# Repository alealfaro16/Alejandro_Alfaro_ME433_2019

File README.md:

# Alejandro_Alfaro_ME433_2019
Mechatronics 433 projects and Hwks

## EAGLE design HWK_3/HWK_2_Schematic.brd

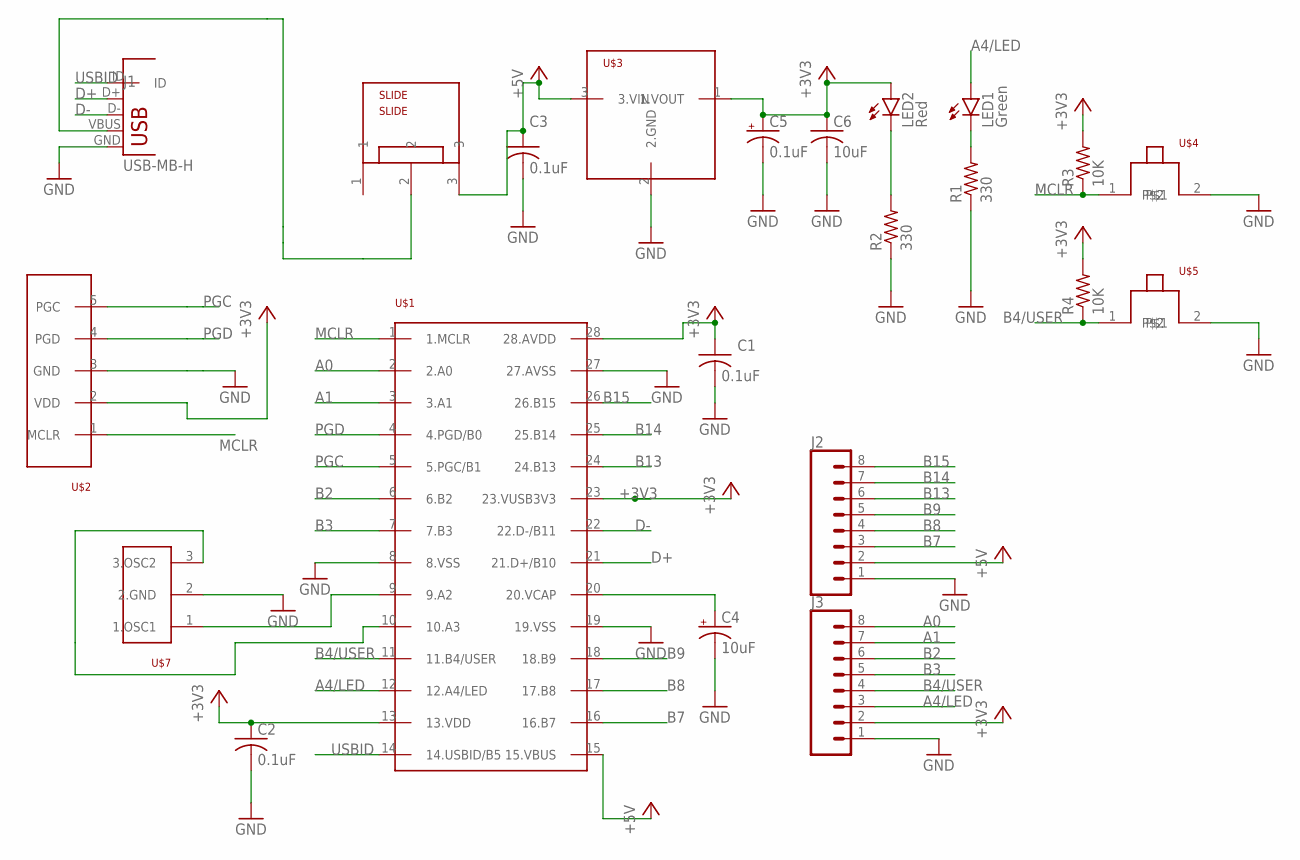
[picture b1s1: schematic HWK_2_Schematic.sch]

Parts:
C1, C2, C3: 0.1uF; C025-025X050
C4: 10uF; B45181B
C5: 0.1uF; B45181B
C6: 10uF; C025-025X050
J1: USB-MB-H
J2, J3: CONN_08NO_SILK_FEMALE_PTH; 1X08_NO_SILK
LED1: Green; LED3MM
LED2: Red; LED3MM
R1, R2: 330; 0207/10
R3, R4: 10K; 0207/10
SLIDE: SLIDE
U$1: PIC32MX250F128B; DIL28-3
U$2: PICKIT3
U$3: VOLTAGE_REGULATOR; TO92
U$4: PUSH_BUTTON
U$5: USER_BUTTON; PUSH_BUTTON
U$7: 8MHz; OSC

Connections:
+3V3: C1.1, C2.1, C5.+, C6.1, J3.2, LED2.A, R3.2, R4.2, U$1.13 (13.VDD), U$1.23 (23.VUSB3V3), U$1.28 (28.AVDD), U$2.2 (VDD), U$3.1 (1.VOUT)
+5V: C3.1, J2.2, SLIDE.3, U$1.15 (15.VBUS), U$3.3 (3.VIN)
A0: J3.8, U$1.2 (2.A0)
A1: J3.7, U$1.3 (3.A1)
A4/LED: J3.3, LED1.A, U$1.12 (12.A4/LED)
B2: J3.6, U$1.6 (6.B2)
B3: J3.5, U$1.7 (7.B3)
B4/USER: J3.4, R4.1, U$1.11 (11.B4/USER), U$5.1
B7: J2.3, U$1.16 (16.B7)
B8: J2.4, U$1.17 (17.B8)
B9: J2.5, U$1.18 (18.B9)
B13: J2.6, U$1.24 (24.B13)
B14: J2.7, U$1.25 (25.B14)
B15: J2.8, U$1.26 (26.B15)
D+: J1.D+, U$1.21 (21.D+/B10)
D-: J1.D-, U$1.22 (22.D-/B11)
GND: C1.2, C2.2, C3.2, C4.-, C5.-, C6.2, J1.GND, J2.1, J3.1, R1.1, R2.1, U$1.8 (8.VSS), U$1.19 (19.VSS), U$1.27 (27.AVSS), U$2.3 (GND), U$3.2 (2.GND), U$4.2, U$5.2, U$7.2 (2.GND)
MCLR: R3.1, U$1.1 (1.MCLR), U$2.1 (MCLR), U$4.1
unnamed: U$1.9 (9.A2), U$7.1 (1.OSC1)
unnamed: J1.VBUS, SLIDE.2
unnamed: LED2.K (C), R2.2
unnamed: U$1.10 (10.A3), U$7.3 (3.OSC2)
unnamed: C4.+, U$1.20 (20.VCAP)
unnamed: LED1.K (C), R1.2
PGC: U$1.5 (5.PGC/B1), U$2.5 (PGC)
PGD: U$1.4 (4.PGD/B0), U$2.4 (PGD)
USBID: J1.ID, U$1.14 (14.USBID/B5)

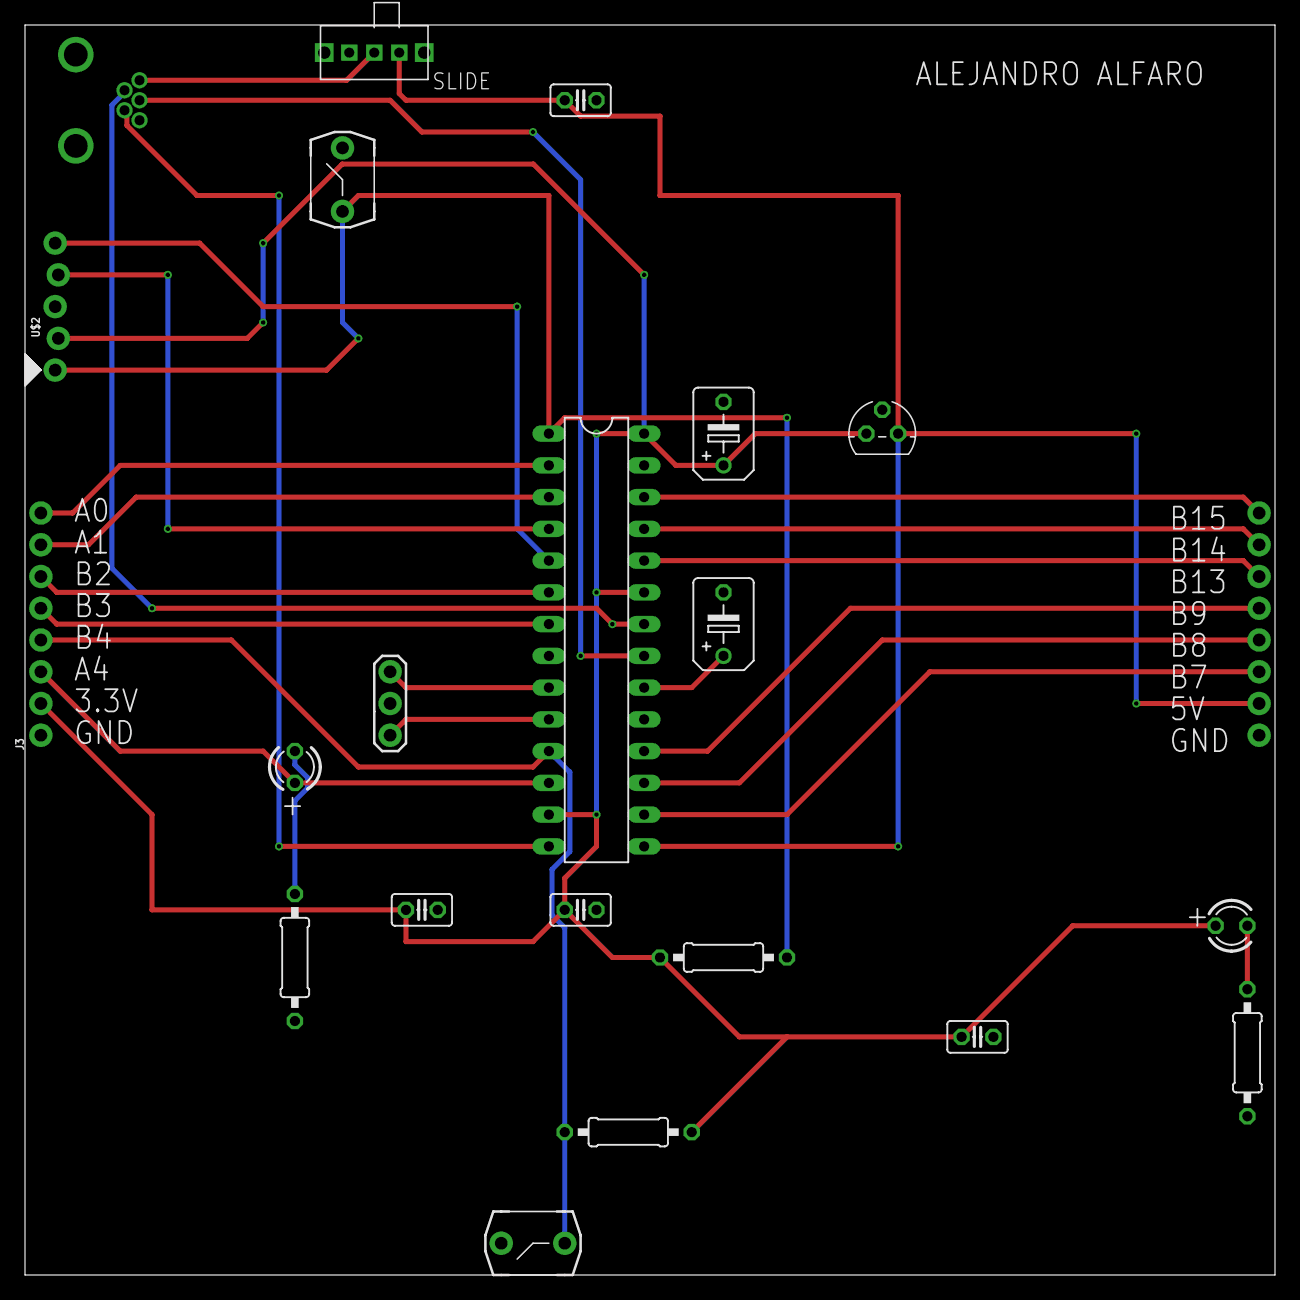
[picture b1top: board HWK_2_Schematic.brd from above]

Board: 2 copper layers, 100.0 x 100.0 mm, 22 parts (0 on the bottom side), 27 nets.

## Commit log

2019-04-04 Hwk 1
2019-04-04 Update Hwk1
2019-04-04 Photo of Breadboard
2019-04-04 Create Code
2019-04-04 Update Code
2019-04-04 Circuit Diagram
2019-04-04 Picture of steady 3.3V supply
2019-04-09 Create PCB Schematic
2019-04-11 Create READ_ME
2019-04-11 Gerber files
2019-04-11 PCB layout
2019-04-11 PCB Schematic
2019-04-17 Screenshot of 2 DAC waves
2019-04-19 Create i2c_master_noint
2019-04-19 Image of Circuit Diagram
2019-04-20 main.c
2019-04-20 Main code
2019-04-20 PIC Setup
2019-04-20 LCD functions
2019-04-21 Photos of Breadboard and Circuit Diagram
2019-04-21 Picture of Breadboard
2019-04-30 Uploaded working main.c
2019-05-06 Harmony code of Hwk 7
2019-05-07 Upload Code
2019-05-07 Create Hwk
2019-05-07 Upload HwK 9 code
2019-05-07 HWK 8 libraries upload
2019-05-14 Harmony code
2019-05-14 Matlab code and plot
2019-05-19 Uploaded code
2019-05-23 CAD design upload
2019-05-23 Pictures upload
2019-05-23 Upload images
2019-06-04 Code
2019-06-14 CAD of Robot
2019-06-14 Pics of robot
